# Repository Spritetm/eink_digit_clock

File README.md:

E-ink digit clock thing
-----------------------

In this repo:

- firmware - Firmware for the ESP32C6. It's intended for ESP-IDF 5.2.0.

- gendigits - code to take digits from a TrueType font, render and compress them

- pcb - PCB artwork for Kicad 8.

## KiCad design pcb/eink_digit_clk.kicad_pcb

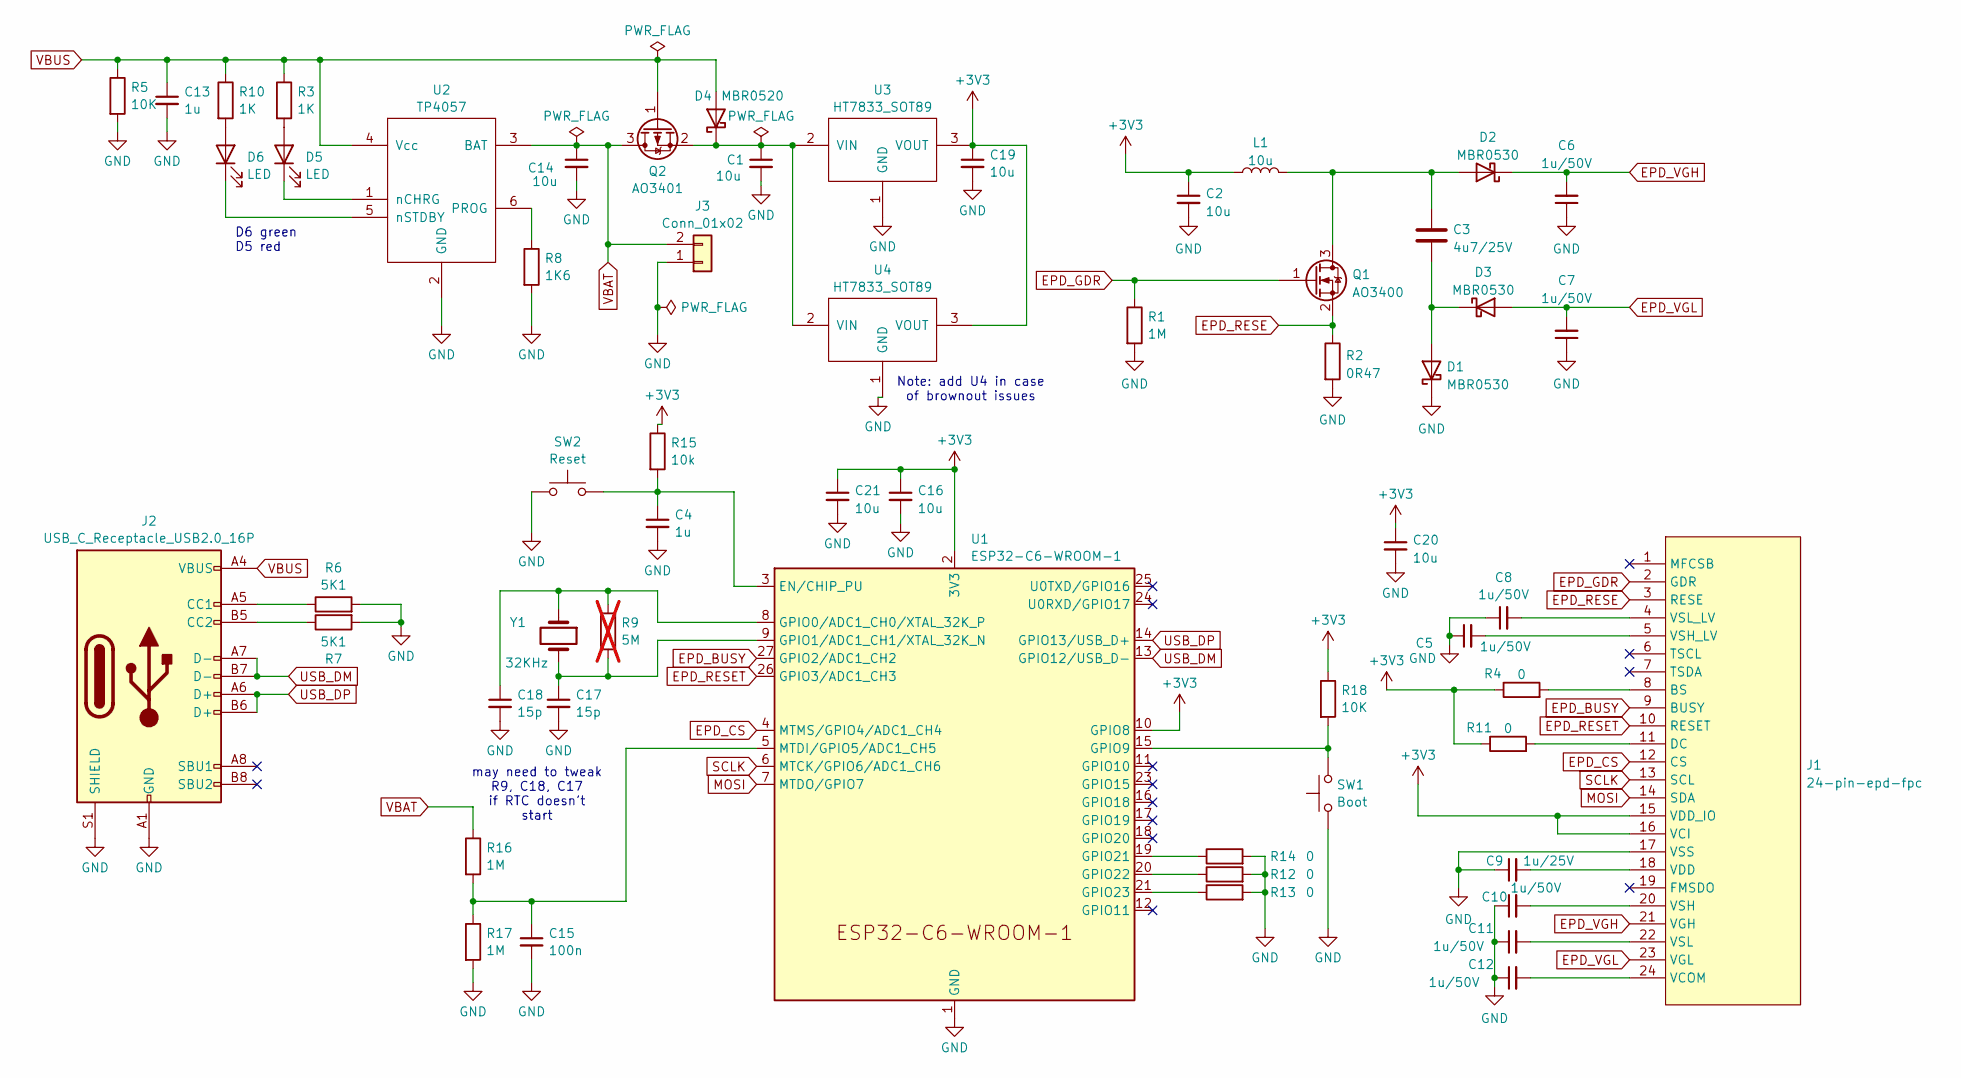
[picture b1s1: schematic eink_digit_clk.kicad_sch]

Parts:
C1, C2, C14, C16, C19, C20, C21: 10u; C_0805_2012Metric
C3: 4u7/25V; C_0603_1608Metric
C4, C13: 1u; C_0603_1608Metric
C5, C6, C7, C8, C10, C11, C12: 1u/50V; C_0603_1608Metric
C9: 1u/25V; C_0603_1608Metric
C15: 100n; C_0603_1608Metric
C17, C18: 15p; C_0603_1608Metric
D1, D2, D3: MBR0530; D_SOD-123
D4: MBR0520; D_SOD-123
D5, D6: LED; LED_0603_1608Metric
J1: 24-pin-epd-fpc; Hirose_FH12-24S-0.5SH_1x24-1MP_P0.50mm_Horizontal_reverse
J2: USB_C_Receptacle_USB2.0_16P; USB_C_Receptacle_HRO_TYPE-C-31-M-12
J3: Conn_01x02; PinHeader_1x02_P2.54mm_Vertical
L1: 10u; L_Sunlord_SWPA4012S
Q1: AO3400; SOT-23
Q2: AO3401; SOT-23
R1, R16, R17: 1M; R_0603_1608Metric
R2: 0R47; R_0603_1608Metric
R3, R10: 1K; R_0603_1608Metric
R4, R11, R12, R13, R14: 0; R_0603_1608Metric
R5, R18: 10K; R_0603_1608Metric
R6, R7: 5K1; R_0603_1608Metric
R8: 1K6; R_0603_1608Metric
R9: 5M; R_0603_1608Metric; not fitted
R15: 10k; R_0603_1608Metric
SW1: Boot; SW_SPST_B3S-1000
SW2: Reset; SW_SPST_B3S-1000
U1: ESP32-C6-WROOM-1
U2: TP4057; SOT-23-6
U3, U4: HT7833_SOT89; SOT-89-3
Y1: 32KHz; Crystal_SMD_3215-2Pin_3.2x1.5mm

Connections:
+3V3: C2.1, C16.1, C19.1, C20.1, C21.1, J1.15 (VDD_IO), J1.16 (VCI), L1.1, R4.1, R11.1, R15.1, R18.1, U1.2 (3V3), U1.10 (GPIO8), U3.3 (VOUT), U4.3 (VOUT)
EPD_BUSY: J1.9 (BUSY), U1.27 (GPIO2/ADC1_CH2)
EPD_CS: J1.12 (CS), U1.4 (MTMS/GPIO4/ADC1_CH4)
EPD_GDR: J1.2 (GDR), Q1.1 (G), R1.1
EPD_RESE: J1.3 (RESE), Q1.2 (S), R2.1
EPD_RESET: J1.10 (RESET), U1.26 (GPIO3/ADC1_CH3)
EPD_VGH: C6.2, D2.1 (K), J1.21 (VGH)
EPD_VGL: C7.2, D3.2 (A), J1.23 (VGL)
GND: C1.2, C2.2, C4.2, C5.1, C6.1, C7.1, C8.1, C9.1, C10.1, C11.1, C12.1, C13.2, C14.2, C15.2, C16.2, C17.2, C18.2, C19.2, C20.2, C21.2, D1.1 (K), J1.17 (VSS), J2.A1 (GND), J2.A12 (GND), J2.B1 (GND), J2.B12 (GND), J2.S1 (SHIELD), J3.1, R1.2, R2.2, R5.2, R6.2, R7.2, R8.2, R12.2, R13.2, R14.2, R17.2, SW1.1, SW2.1, U1.1 (GND), U1.28 (GND), U1.29 (GND), U2.2 (GND), U3.1 (GND), U4.1 (GND)
MOSI: J1.14 (SDA), U1.7 (MTDO/GPIO7)
unnamed: C3.2, D1.2 (A), D3.1 (K)
unnamed: C3.1, D2.2 (A), L1.2, Q1.3 (D)
unnamed: C1.1, D4.1 (K), Q2.2 (S), U3.2 (VIN), U4.2 (VIN)
unnamed: D5.2 (A), R3.2
unnamed: D5.1 (K), U2.1 (nCHRG)
unnamed: D6.2 (A), R10.2
unnamed: D6.1 (K), U2.5 (nSTDBY)
unnamed: J1.8 (BS), R4.2
unnamed: J1.11 (DC), R11.2
unnamed: C12.2, J1.24 (VCOM)
unnamed: C9.2, J1.18 (VDD)
unnamed: C10.2, J1.20 (VSH)
unnamed: C5.2, J1.5 (VSH_LV)
unnamed: C11.2, J1.22 (VSL)
unnamed: C8.2, J1.4 (VSL_LV)
unnamed: J2.A5 (CC1), R6.1
unnamed: J2.B5 (CC2), R7.1
unnamed: C4.1, R15.2, SW2.2, U1.3 (EN/CHIP_PU)
unnamed: C18.1, R9.1, U1.8 (GPIO0/ADC1_CH0/XTAL_32K_P), Y1.1
unnamed: C17.1, R9.2, U1.9 (GPIO1/ADC1_CH1/XTAL_32K_N), Y1.2
unnamed: R18.2, SW1.2, U1.15 (GPIO9)
unnamed: R14.1, U1.19 (GPIO21)
unnamed: R12.1, U1.20 (GPIO22)
unnamed: R13.1, U1.21 (GPIO23)
unnamed: C15.1, R16.2, R17.1, U1.5 (MTDI/GPIO5/ADC1_CH5)
unnamed: R8.1, U2.6 (PROG)
SCLK: J1.13 (SCL), U1.6 (MTCK/GPIO6/ADC1_CH6)
USB_DM: J2.A7 (D-), J2.B7 (D-), U1.13 (GPIO12/USB_D-)
USB_DP: J2.A6 (D+), J2.B6 (D+), U1.14 (GPIO13/USB_D+)
VBAT: C14.1, J3.2, Q2.3 (D), R16.1, U2.3 (BAT)
VBUS: C13.1, D4.2 (A), J2.A4 (VBUS), J2.A9 (VBUS), J2.B4 (VBUS), J2.B9 (VBUS), Q2.1 (G), R3.1, R5.1, R10.1, U2.4 (Vcc)

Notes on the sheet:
may need to tweak R9, C18, C17 if RTC doesn't start
D6 green D5 red
Note: add U4 in case of brownout issues

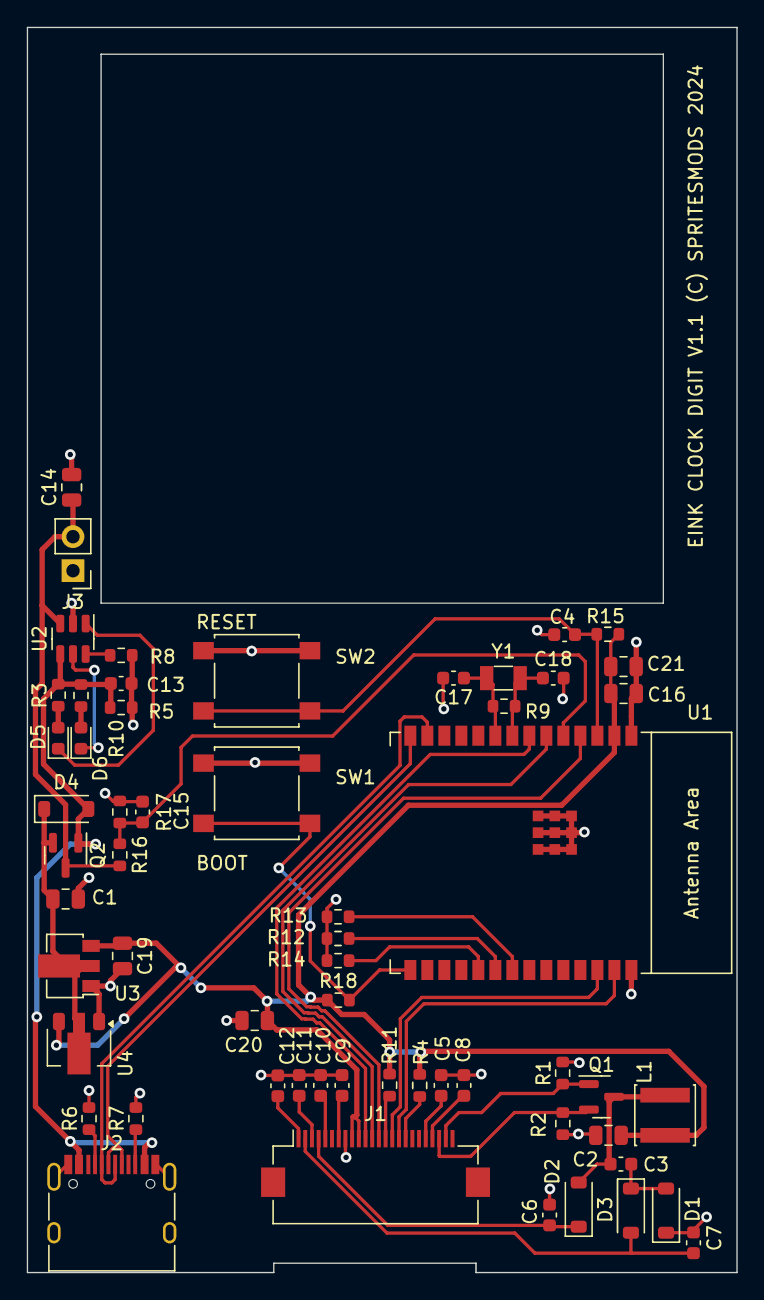
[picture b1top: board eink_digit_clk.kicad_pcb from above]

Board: 2 copper layers, 53.0 x 93.0 mm, 58 parts (0 on the bottom side), 41 nets.

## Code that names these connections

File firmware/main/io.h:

//IO definitions

#define IO_EPD_BUSY 2
#define IO_EPD_RESET 3
#define IO_EPD_CS 4
#define IO_EPD_SCLK 6
#define IO_EPD_MOSI 7

#define IO_ID0 21
#define IO_ID1 22
#define IO_ID2 23

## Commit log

2024-03-09 Initial commit. Got ULP displaying numbers.
2024-03-14 It works, but with ntp sync, so the digits will drift apart
2024-06-04 Fix issues in schematic/pcb
2024-06-04 Show errors if something goes wrong
2024-06-04 Add some comments, add licenses
2024-06-04 Add readme
2024-07-21 Comments
